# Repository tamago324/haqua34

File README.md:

# haqua34

* gku34 を割ったキーボード
* 割った以外は gku34 と同じ
    * 狭ピッチ
    * キーピッチが縦17mmx横18mm
    * KiCad 6 で作成
    * [horizon プラグイン](https://github.com/skarrmann/horizon/blob/5833ec133d5f8fa4f3824622efd5dbfc89d797ec/kicad-plugins/horizon-board-producer-plugin.py)を使ってボトムプレートを生成
    * choc v1 と Lofree switch 対応

|||
|---|---|
|left|right|

## Firmware

[keyboard-firmwares](https://github.com/tamago324/keyboard-firmwares) 内の `keybaords/haqua34`

## LICENSE

<br />この 作品 は <a rel="license" href="http://creativecommons.org/licenses/by-nc/4.0/">クリエイティブ・コモンズ 表示 - 非営利 4.0 国際 ライセンス</a>の下に提供されています。

> 表示 — あなたは 適切なクレジットを表示し、ライセンスへのリンクを提供し、変更があったらその旨を示さなければなりません。これらは合理的であればどのような方法で行っても構いませんが、許諾者があなたやあなたの利用行為を支持していると示唆するような方法は除きます。
>
> 非営利 — あなたは営利目的でこの資料を利用してはなりません。

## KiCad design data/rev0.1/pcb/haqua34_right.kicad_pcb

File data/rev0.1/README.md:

## 発注するとき (JLCPCB)

* 基板
  * main_pcb (メイン基板)
    * left: `gerbers/left_main_pcb/haqua34_left_134.025522x114.635239mm_for_JLCPCB.zip`
      * PCB Thickness: 1.6mm
      * Remove Order Number: Specify a location
    * right: `gerbers/right_main_pcb/haqua34_right_134.025517x114.635239mm_for_JLCPCB.zip`
      * PCB Thickness: 1.6mm
      * Remove Order Number: Specify a location
  * bottom_plate (ボトムプレート)
    * left: `gerbers/left_bottom_plate/haqua34_left-bottom-plate_134.025522x114.635239mm_for_JLCPCB.zip`
      * PCB Thickness: 1.6mm
      * Remove Order Number: Specify a location
    * right: `gerbers/right_bottom_plate/haqua34_right-bottom-plate_134.025517x114.635239mm_for_JLCPCB.zip`
      * PCB Thickness: 1.6mm
      * Remove Order Number: Specify a location
* トッププレート
  * left: `stl/top_plate_left.stl`
    * 3D Technology: MJF(Nylon)
    * Material: PA12-HP Nylon
    * Color: Black
  * right: `stl/top_plate_right.stl`
    * 3D Technology: MJF(Nylon)
    * Material: PA12-HP Nylon
    * Color: Black

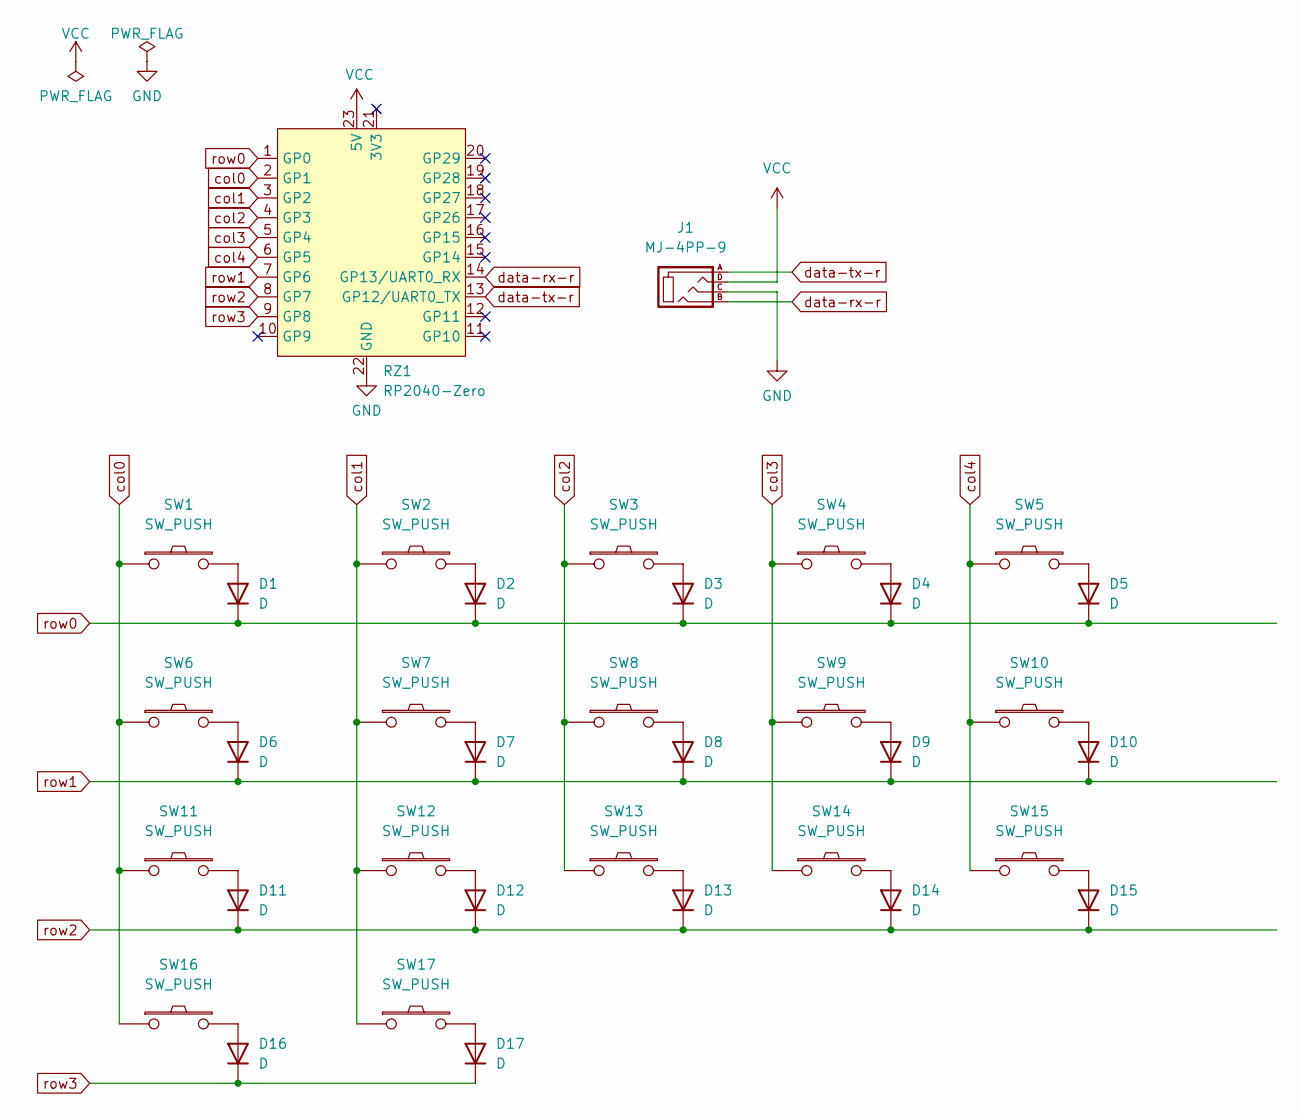
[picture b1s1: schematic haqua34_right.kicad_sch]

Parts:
D1, D2, D3, D4, D5, D6, D7, D8, D9, D10, D11, D12, D13, D14, D15, D16, D17: D; Diode_SMD
J1: MJ-4PP-9
RZ1: RP2040-Zero
SW1, SW2, SW3, SW4, SW5, SW6, SW7, SW8, SW9, SW10, SW11, SW12, SW13, SW14, SW15, SW16, SW17: SW_PUSH; SW_Choc_V2

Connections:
GND: J1.C, RZ1.22 (GND)
unnamed: D1.2 (A), SW1.2
unnamed: D2.2 (A), SW2.2
unnamed: D3.2 (A), SW3.2
unnamed: D4.2 (A), SW4.2
unnamed: D5.2 (A), SW5.2
unnamed: D6.2 (A), SW6.2
unnamed: D7.2 (A), SW7.2
unnamed: D8.2 (A), SW8.2
unnamed: D9.2 (A), SW9.2
unnamed: D10.2 (A), SW10.2
unnamed: D11.2 (A), SW11.2
unnamed: D12.2 (A), SW12.2
unnamed: D13.2 (A), SW13.2
unnamed: D14.2 (A), SW14.2
unnamed: D15.2 (A), SW15.2
unnamed: D16.2 (A), SW16.2
unnamed: D17.2 (A), SW17.2
VCC: J1.D, RZ1.23 (5V)
col0: RZ1.2 (GP1), SW1.1, SW6.1, SW11.1, SW16.1
col1: RZ1.3 (GP2), SW2.1, SW7.1, SW12.1, SW17.1
col2: RZ1.4 (GP3), SW3.1, SW8.1, SW13.1
col3: RZ1.5 (GP4), SW4.1, SW9.1, SW14.1
col4: RZ1.6 (GP5), SW5.1, SW10.1, SW15.1
data-rx-r: J1.B, RZ1.14 (GP13/UART0_RX)
data-tx-r: J1.A, RZ1.13 (GP12/UART0_TX)
row0: D1.1 (K), D2.1 (K), D3.1 (K), D4.1 (K), D5.1 (K), RZ1.1 (GP0)
row1: D6.1 (K), D7.1 (K), D8.1 (K), D9.1 (K), D10.1 (K), RZ1.7 (GP6)
row2: D11.1 (K), D12.1 (K), D13.1 (K), D14.1 (K), D15.1 (K), RZ1.8 (GP7)
row3: D16.1 (K), D17.1 (K), RZ1.9 (GP8)

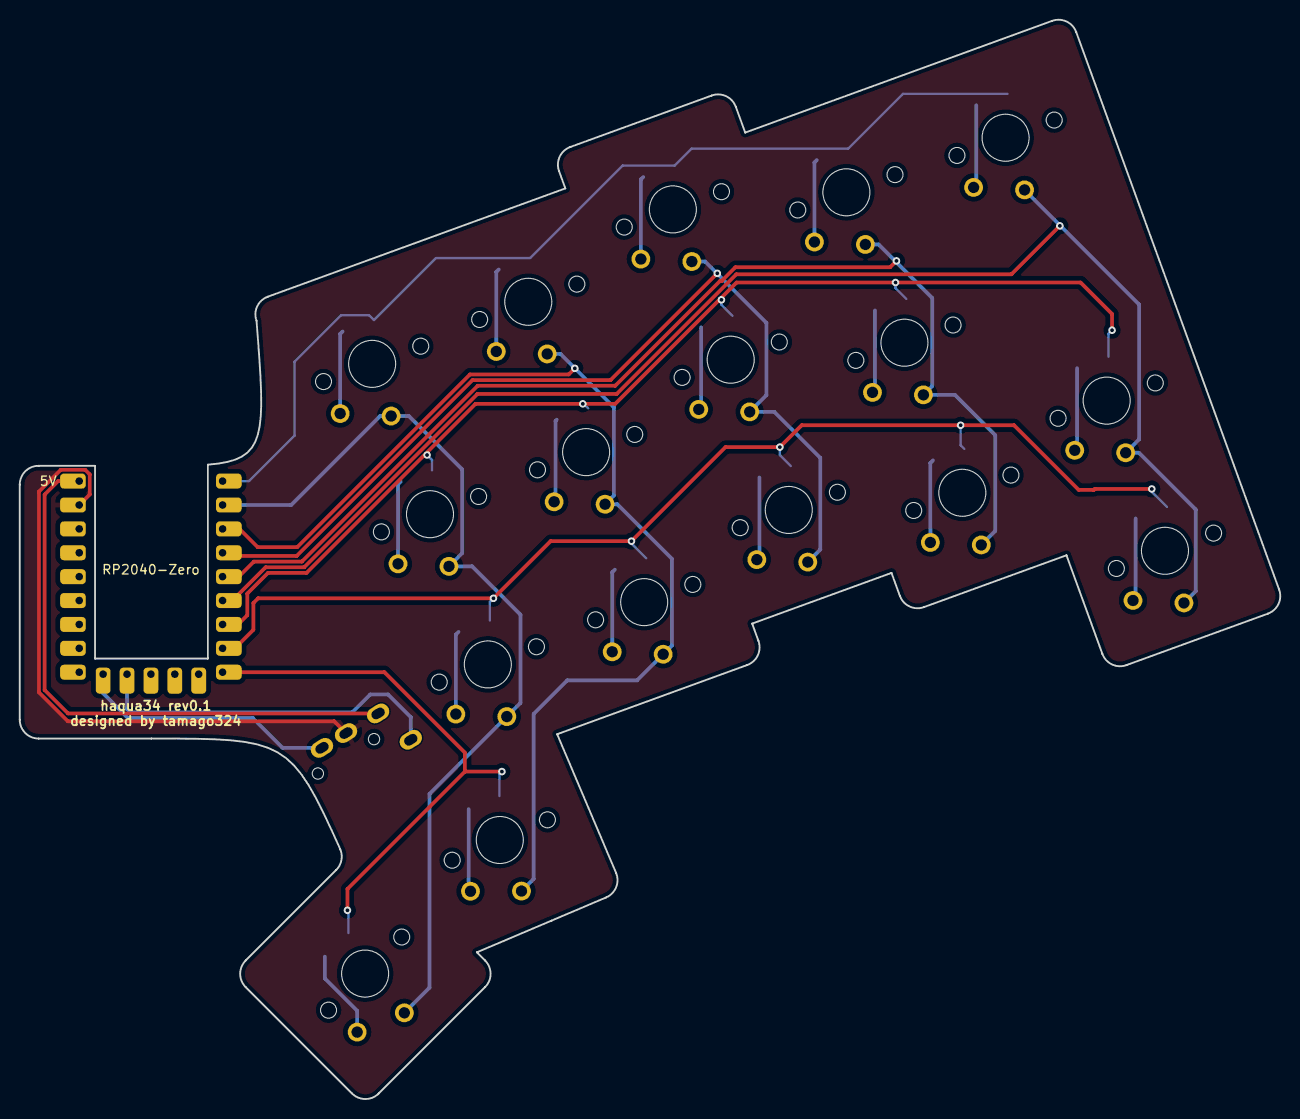
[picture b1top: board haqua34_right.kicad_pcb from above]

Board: 2 copper layers, 134.0 x 114.8 mm, 36 parts (0 on the bottom side), 30 nets.

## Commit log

2024-04-13 init
2024-04-13 データの修正
2024-05-02 add buildguide.md
2024-05-02 fix buildguide.md
2024-05-02 updsate buildguide.md
2024-05-04 update buildguide

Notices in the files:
README.md:
LICENSE:
CC BY-NC 4.0
